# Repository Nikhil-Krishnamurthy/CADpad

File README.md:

# CADpad
Macropad designed from scratch for cad, media, and coding. Along with a custom script to run badapple on the oled screen!  
Note that the pcb has the scl and sca pins mixed up on it, I just cut the traces and ran a wire around it.  
  
Key Features  
Macropad with 11 reprogrammable keys  
oled screen that displays layers and animations  
rotary encoder that interfaces with computer  
interface with the computer for input and output  
And of course, it can run bad apple  

BOM  
12x 1n4148 Diodes  
1x EC11 Encoders  
1x 0.91 in OLED display  
11x DSA keycaps  
11x Cherry MX Keycaps  
1x XIAO RP2040  
1X Case (3d Printed)  
4x M3 16mm screws  
4x M3x5mmx4mm Heat Inserts

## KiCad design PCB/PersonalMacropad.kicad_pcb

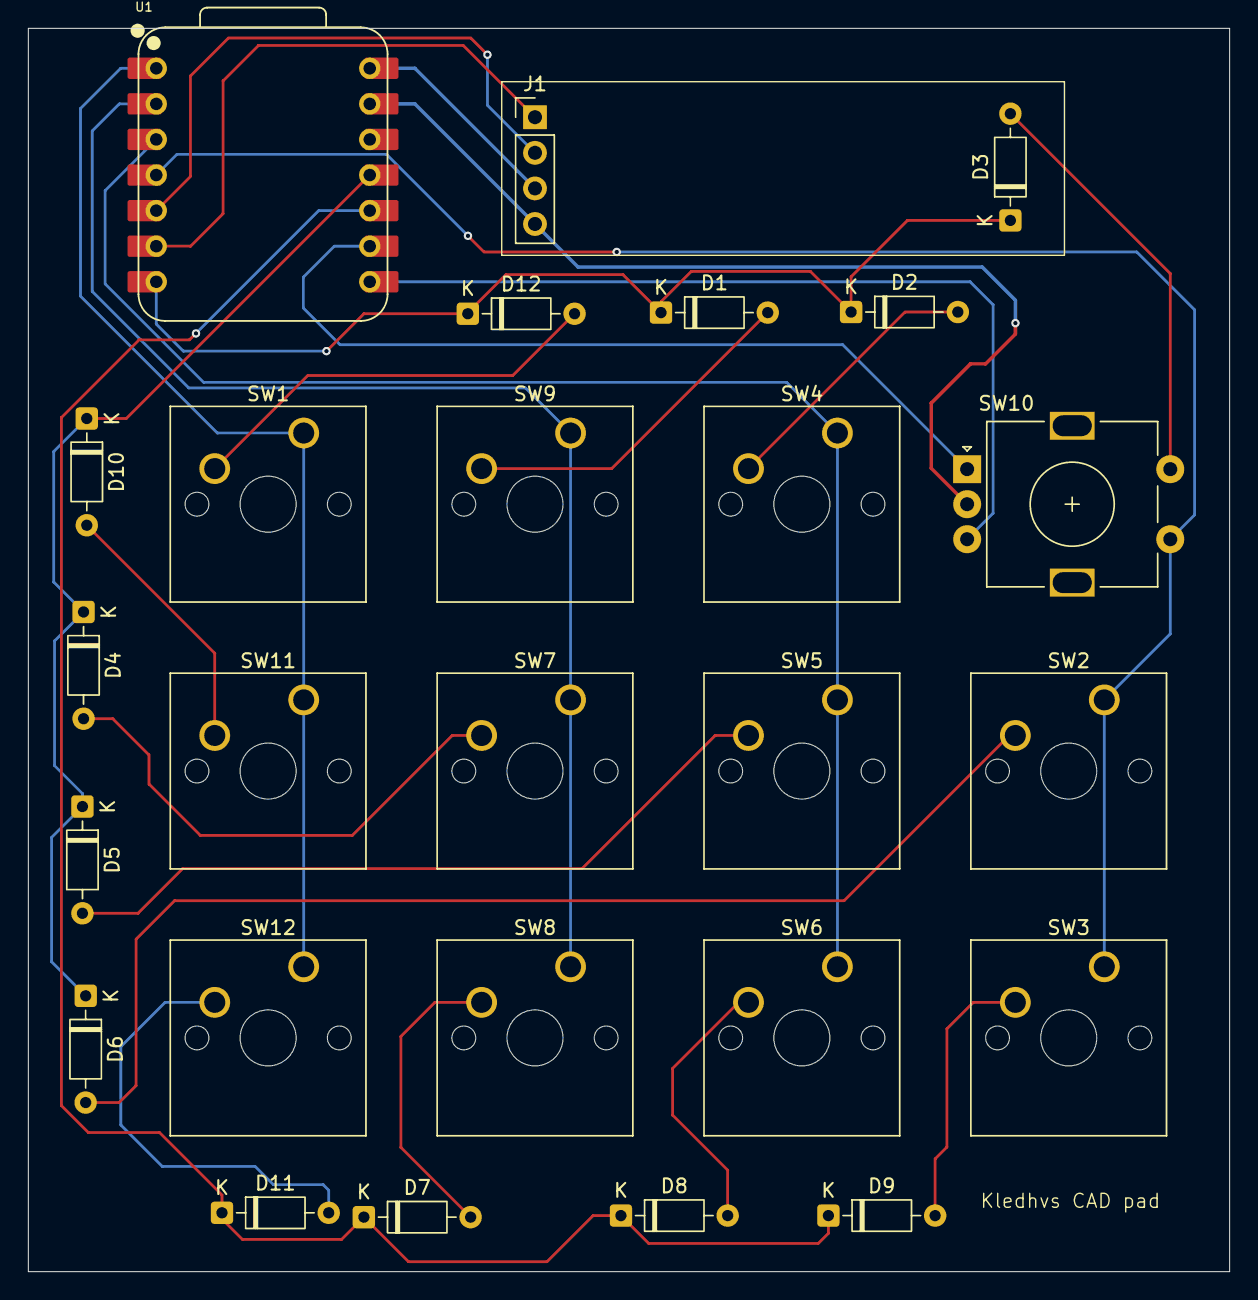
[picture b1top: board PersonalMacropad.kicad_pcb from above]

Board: 2 copper layers, 85.7 x 88.8 mm, 26 parts (0 on the bottom side), 25 nets.

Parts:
D1, D2, D3, D4, D5, D6, D7, D8, D9, D10, D11, D12: 1N4148; D_DO-35_SOD27_P7.62mm_Horizontal
J1: OLED Display; PinHeader_1x04_P2.54mm_Vertical
SW1, SW2, SW3, SW4, SW5, SW6, SW7, SW8, SW9, SW11, SW12: SW_Push; SW_Cherry_MX_1.00u_PCB
SW10: RotaryEncoder_Switch; RotaryEncoder_Alps_EC11E-Switch_Vertical_H20mm
U1: XIAO-RP2040-DIP

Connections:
Col0: SW1.1, SW11.1, SW12.1, U1.1 (GPIO26/ADC0/A0)
Col1: SW7.1, SW8.1, SW9.1, U1.2 (GPIO27/ADC1/A1)
Col2: SW4.1, SW5.1, SW6.1, U1.3 (GPIO28/ADC2/A2)
Col3: SW2.1, SW3.1, SW10.S1, U1.4 (GPIO29/ADC3/A3)
EC11A: SW10.A, U1.9 (GPIO2/SCK)
EC11B: SW10.B, U1.8 (GPIO1/RX)
GND: J1.4, SW10.C, U1.13 (GND)
unnamed: D1.2 (A), SW9.2
unnamed: D2.2 (A), SW4.2
unnamed: D3.2 (A), SW10.S2
unnamed: D4.2 (A), SW7.2
unnamed: D5.2 (A), SW5.2
unnamed: D6.2 (A), SW2.2
unnamed: D7.2 (A), SW8.2
unnamed: D8.2 (A), SW6.2
unnamed: D9.2 (A), SW3.2
unnamed: D10.2 (A), SW11.2
unnamed: D11.2 (A), SW12.2
unnamed: D12.2 (A), SW1.2
Row0: D1.1 (K), D2.1 (K), D3.1 (K), D12.1 (K), U1.7 (GPIO0/TX)
Row1: D4.1 (K), D5.1 (K), D6.1 (K), D10.1 (K), U1.11 (GPIO3/MOSI)
Row2: D7.1 (K), D8.1 (K), D9.1 (K), D11.1 (K), U1.10 (GPIO4/MISO)
SCL: J1.1, U1.6 (GPIO7/SCL)
SDA: J1.2, U1.5 (GPIO6/SDA)
VCC: J1.3, U1.14 (VBUS)

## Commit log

2026-01-30 Uploaded Files
    Allows for others to use.
2026-03-04 New finished product
2026-03-04 readme overhaul
2026-03-04 added directions to firmware
